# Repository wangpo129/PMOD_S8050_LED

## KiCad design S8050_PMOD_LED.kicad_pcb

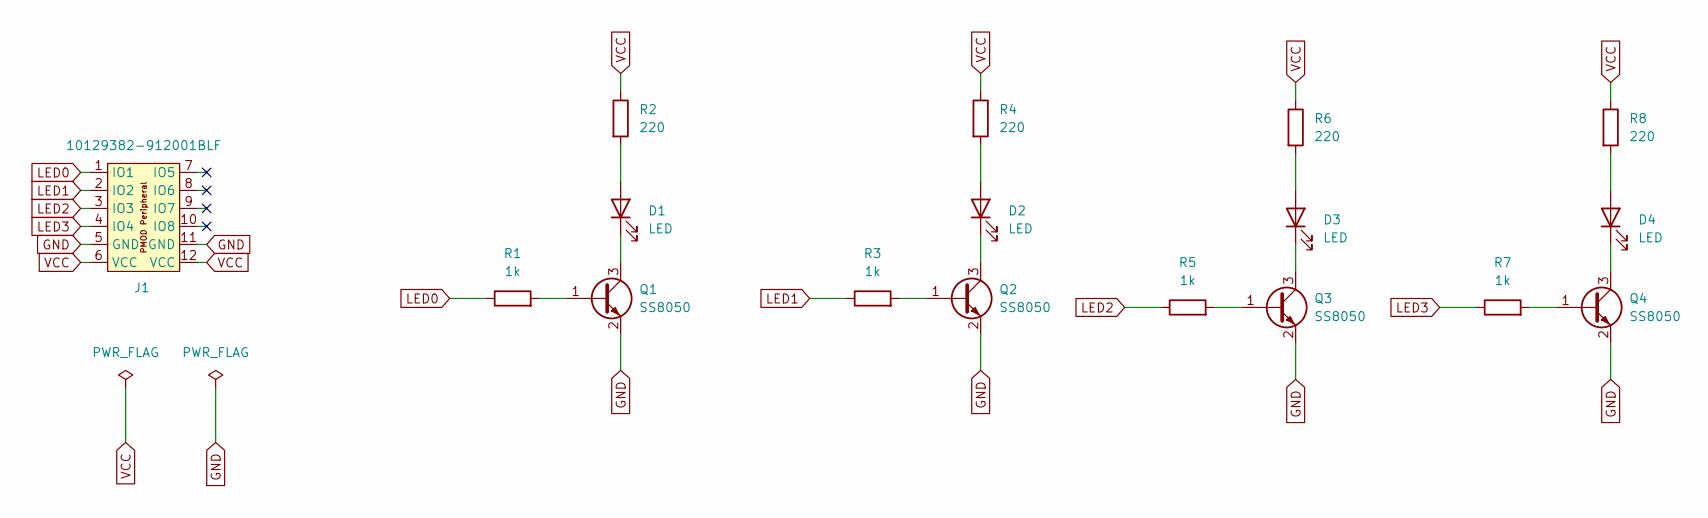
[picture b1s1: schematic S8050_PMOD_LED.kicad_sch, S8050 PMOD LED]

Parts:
D1, D2, D3, D4: LED; LED_0603_1608Metric
J1: 10129382-912001BLF; PinHeader_2x06_P2.54mm_PMODPeriph2B; LCSC Part C492434
Q1, Q2, Q3, Q4: SS8050; SOT-23
R1, R3, R5, R7: 1k; R_0603_1608Metric
R2, R4, R6, R8: 220; R_0603_1608Metric

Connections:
GND: J1.5 (GND), J1.11 (GND), Q1.2 (E), Q2.2 (E), Q3.2 (E), Q4.2 (E)
LED0: J1.1 (IO1), R1.1
LED1: J1.2 (IO2), R3.1
LED2: J1.3 (IO3), R5.1
LED3: J1.4 (IO4), R7.1
unnamed: D1.2 (A), R2.2
unnamed: D1.1 (K), Q1.3 (C)
unnamed: D2.2 (A), R4.2
unnamed: D2.1 (K), Q2.3 (C)
unnamed: D3.2 (A), R6.2
unnamed: D3.1 (K), Q3.3 (C)
unnamed: D4.2 (A), R8.2
unnamed: D4.1 (K), Q4.3 (C)
unnamed: Q1.1 (B), R1.2
unnamed: Q2.1 (B), R3.2
unnamed: Q3.1 (B), R5.2
unnamed: Q4.1 (B), R7.2
VCC: J1.6 (VCC), J1.12 (VCC), R2.1, R4.1, R6.1, R8.1

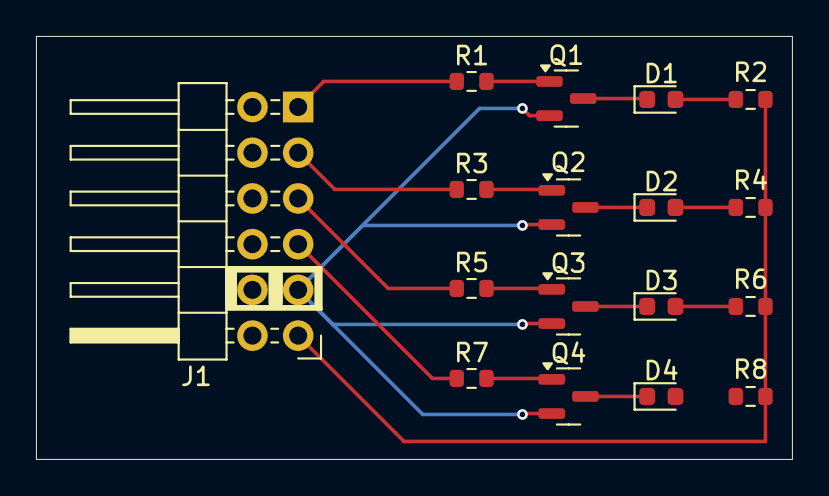
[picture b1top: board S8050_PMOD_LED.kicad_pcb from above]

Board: 2 copper layers, 42.0 x 23.5 mm, 17 parts (0 on the bottom side), 18 nets.

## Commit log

2025-06-15 版本1.0，双面布线，S8050驱动
